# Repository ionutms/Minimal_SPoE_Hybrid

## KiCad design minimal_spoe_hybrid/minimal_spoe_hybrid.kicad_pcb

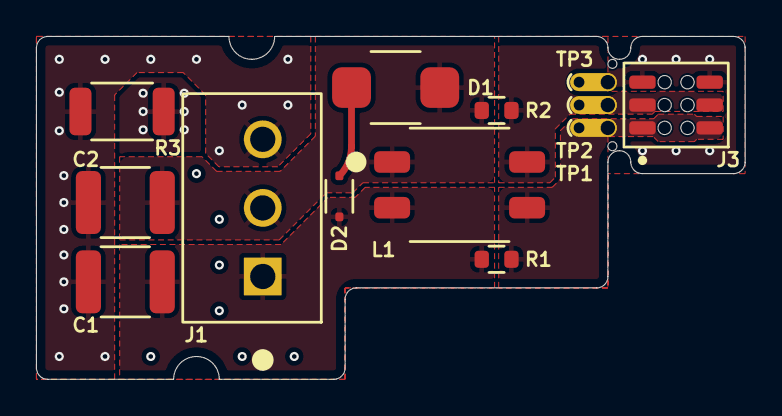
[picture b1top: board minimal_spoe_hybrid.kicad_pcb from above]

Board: 4 copper layers, 39.4 x 19.0 mm, 14 parts (0 on the bottom side), 7 nets.

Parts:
C1, C2: 100 pF; C_1812_4532Metric
D1: 58 V; DO-214AA
D2: 3.3 V; SOD323
J1: TBP02R2-381; TBP02R2-381-03BE
J3: CLP-103-02-G-D-BE
L1: 470 µH; SRF0905A
MB1: mouse-bite-midle-50mil-200mil; mouse-bite-midle-50mil-250mil
R1, R2: 10 kΩ; R_0603_1608Metric
R3: 4.7 MΩ; R_2010_5025Metric
TP1, TP2, TP3: TestPoint; TestPoint_THTPad_Castelated

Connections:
/CABLE+: C1.1, D2.1, J1.1, L1.2, R1.1
/CABLE-: C2.1, D1.2, J1.2, L1.1, R2.1
/DATA_AND_POWER_N: J3.3, J3.4, L1.4, R2.2, TP2.1
/DATA_AND_POWER_P: J3.1, J3.2, L1.3, R1.2, TP1.1
Earth: C1.2, C2.2, J1.3, R3.1
GND: J3.5, J3.6, R3.2, TP3.1
unnamed: D1.1, D2.2

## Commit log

2025-03-04 Add initial KiCad project files for minimal_spoe_hybrid
2025-03-04 Add submodule for KiCAD Symbol Generator
2025-03-04 Add footprint and symbol library tables for KiCad project
2025-03-04 Update KiCAD Symbol Generator submodule to latest commit
2025-03-05 Update KiCAD Symbol Generator submodule and modify project settings
2025-03-06 Update KiCAD Symbol Generator submodule and modify project configuration
2025-03-07 Update KiCAD Symbol Generator submodule and remove unused circle elements from schematic
2025-03-07 Update KiCAD Symbol Generator submodule and clean up project configuration
2025-03-08 Update KiCAD Symbol Generator submodule and regenerate PDF schematic
2025-03-10 Add minimal_spoe_hybrid.glb and update KiCAD Symbol Generator submodule
2025-03-16 Removed KiCAD Symbol Generator submodule
2025-03-16 Backup
2025-03-16 Add KiCAD Symbol Generator submodule configuration
2025-03-16 Remove KiCAD Symbol Generator submodule configuration and files
2025-03-16 Remove KiCAD Symbol Generator submodule and configuration
2025-03-16 Add KiCAD Symbols Generator submodule configuration
2025-03-16 Update KiCAD library paths to use Symbols Generator
2025-03-16 Update KiCAD Symbols Generator submodule to latest commit
2025-03-18 Switch to KiCad 9
2025-03-19 Add .log files to .gitignore
2025-03-19 Add project job set configuration for minimal_spoe_hybrid
2025-03-19 Add minimal_spoe_hybrid assets and update project configuration
2025-03-19 Refactor project job set configuration for minimal_spoe_hybrid to streamline 3D export settings
2025-03-19 Update minimal_spoe_hybrid assets with new GLB and PNG files
2025-03-20 Add new special_execute command for rendering minimal_spoe_hybrid PCB
2025-03-20 Update subproject commit for KiCAD Symbols Generator in minimal_spoe_hybrid
2025-03-20 Add new assets and update project configuration for minimal_spoe_hybrid
2025-03-21 Update export commands and output paths in project job set for minimal_spoe_hybrid
2025-03-21 Remove outdated images and add new 3D model and picture assets for minimal_spoe_hybrid
